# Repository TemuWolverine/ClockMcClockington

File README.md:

# ClockMcClockington
I currently have some “Lenovo Smart Clock Essentials” around the house, but they’ll need to be returned to the original owner soon. Essentially they’re just a segment display with some smarts and a microphone for Google Home.

I’m no fan of voice assistance, so the microphone has been off, meaning they don’t provide much real world value for me other than a clock and that should be easy enough to replicate with an ESP32 and ESPHome.

Since all of the smarts in my house run off Home Assistant (HA), I want this clock to be able to interact with HA. Specifically, I want some buttons that can then trigger other things in the house, such as “shut down all the lights”, or “volume up/down” for the bedroom Sonos speakers. That way I don’t need to have my phone on.

## BoM
| Part | Quantity | Note |
| -----| -------- | ---- |
| [ESP32-S3 Nano](https://s.click.aliexpress.com/e/_c4kUQqIB) | 1 | If you're using the ClockMcClockington PCB, it is designed for this specific ESP32. Otherwise, any S3 with 2MB of PSRAM should be fine |
| [5mm Tactile switches](https://s.click.aliexpress.com/e/_c4DqcA55) | 4 | |
| [GL5516 LDR Photoresistor](https://s.click.aliexpress.com/e/_c41f2RgX) | 1 | |
| [INMP441 Microphone](https://www.aliexpress.com/item/1005006090551057.html) | 1 | |
| [MAX98357a amplifier](https://www.aliexpress.com/item/1005007003802663.html) | 1 | |
| Speaker | 1 | |
|  0.1uf ceramic capacitor | 2| Decoupling, through-hole|
| 10k ohm resistor | 1 | Through-hole|
| ClockMcClockington PCB | 1 | Optional|

## Software
The ESPHome configuration is available as the [yaml file](https://github.com/TemuWolverine/ClockMcClockington/blob/main/clock.yaml), or as a [binary you can flash directly from your browser](https://temuwolverine.github.io/ClockMcClockington/)

### Setup
The temperature information is fetched from Home Assistant. You'll need to have the sensor preconfigured.

* Setup a template sensor
* Navigate (in Home Assistant) to Settings > Devices & Services > Helpers
* Create Helper (bottom right corner) > Template > Sensor
* Two fields are required, the name and the state. Name must be `clock_temp`
* Set the state to `{{ states("sensor.myweathersensor_temperature")}}`
  The other fields are entirely optional, but can make presentation in HomeAssistant clearer 

Alternatively, you can edit the YAML, change `weatherSensor : sensor.clock_temp` to `weatherSensor : sensor.sensor.myweathersensor_temperature`

### Automations
The way ESPHome exposes hardware buttons to Home Assistant is a bit funky (or I'm an idiot and have done it wrong) - they're exposed as generic events rather than 'click'.

ClockMcClockington sends out `esphome.<name>.clock_button_pressed`, where name will start with 'clockmcclockington' plus the MAC of the device. The event data will be one, two, three or four. Currently long press and double click are not implemented. 
```yaml
alias: btnOne
description: ""
triggers:
  - trigger: event
    event_data:
      button: one
    event_type: esphome.clockmcclockingtonred.clock_button_pressed
conditions: []
actions:
  - action: light.toggle
    metadata: {}
    target:
      area_id: study
    data: {}
mode: single
```

## Shell
TODO: 

## Circuit
The Kicad project for the circuit design is available under the [/circuit](https://github.com/TemuWolverine/ClockMcClockington/tree/main/circuit) folder

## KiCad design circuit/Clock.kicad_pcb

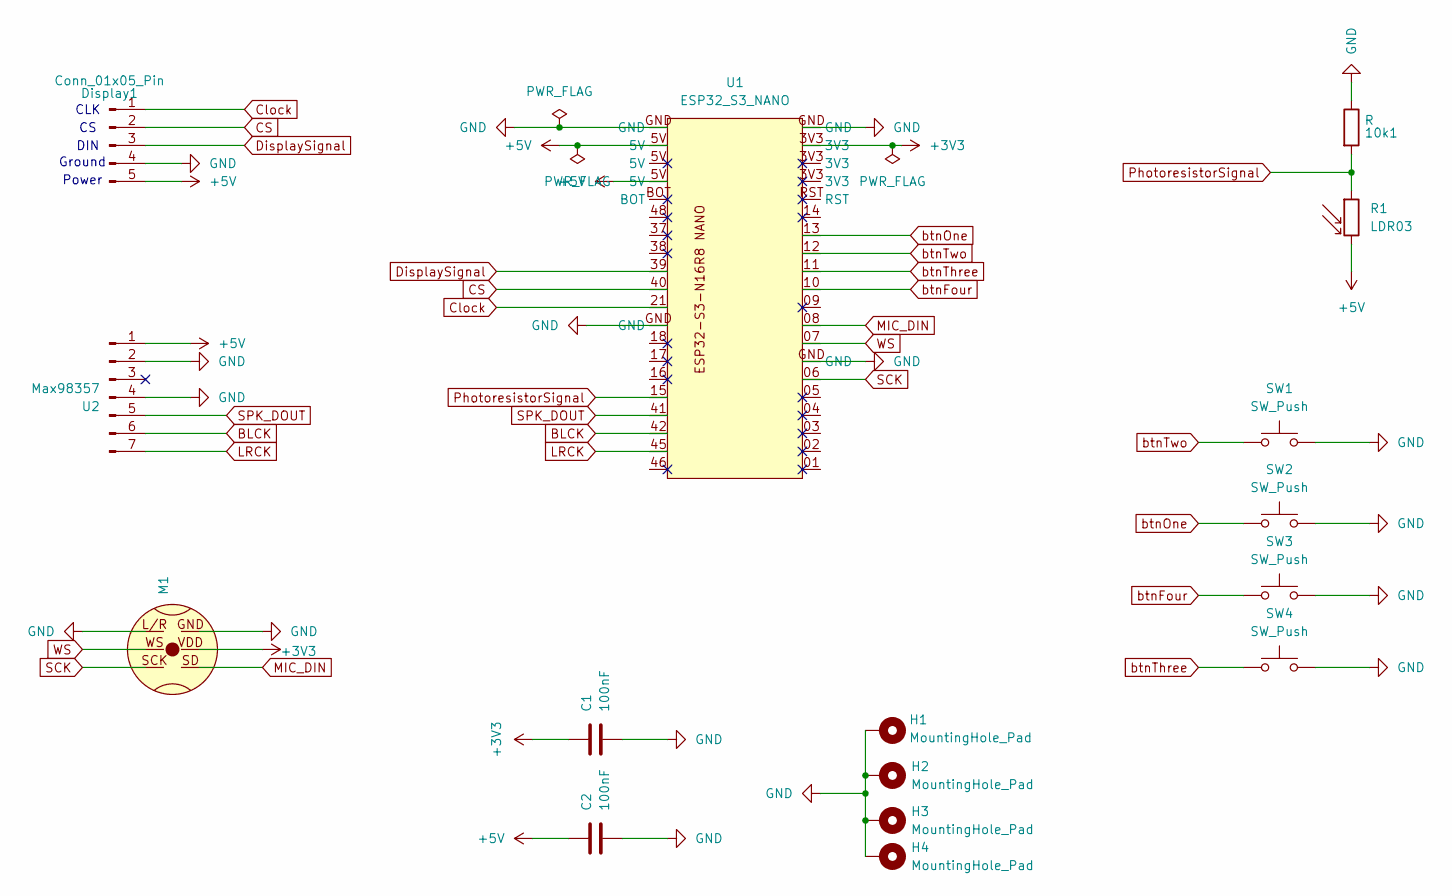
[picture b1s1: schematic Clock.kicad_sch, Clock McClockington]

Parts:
10k1: R; R_Axial_DIN0204_L3.6mm_D1.6mm_P2.54mm_Vertical
C1, C2: 100nF; C_Disc_D8.0mm_W2.5mm_P5.00mm
Display1: Conn_01x05_Pin; PinSocket_1x05_P2.54mm_Vertical
H1, H2, H3, H4: MountingHole_Pad; MountingHole_3.2mm_M3_Pad
M1: INMP441
R1: LDR03; R_LDR_4.9x4.2mm_P2.54mm_Vertical
SW1, SW2, SW3, SW4: SW_Push; SW_PUSH_6mm_H5mm
U1: ESP32_S3_NANO
U2: Max98357; PinHeader_1x07_P2.54mm_Vertical

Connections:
+3V3: C1.1, M1.VDD, U1.3V3
+5V: C2.1, Display1.5, R1.2, U1.5V, U2.1
BLCK: U1.42, U2.6
CS: Display1.2, U1.40
Clock: Display1.1, U1.21
DisplaySignal: Display1.3, U1.39
GND: 10k1.1, C1.2, C2.2, Display1.4, H1.1 (1_1), H2.1 (1_1), H3.1 (1_1), H4.1 (1_1), M1.GND, M1.L/R, SW1.2, SW2.2, SW3.2, SW4.2, U1.GND, U2.2, U2.4
LRCK: U1.45, U2.7
MIC_DIN: M1.SD, U1.08
PhotoresistorSignal: 10k1.2, R1.1, U1.15
SCK: M1.SCK, U1.06
SPK_DOUT: U1.41, U2.5
WS: M1.WS, U1.07
btnFour: SW3.1, U1.10
btnOne: SW2.1, U1.13
btnThree: SW4.1, U1.11
btnTwo: SW1.1, U1.12

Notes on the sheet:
CLK
Power
DIN
Ground

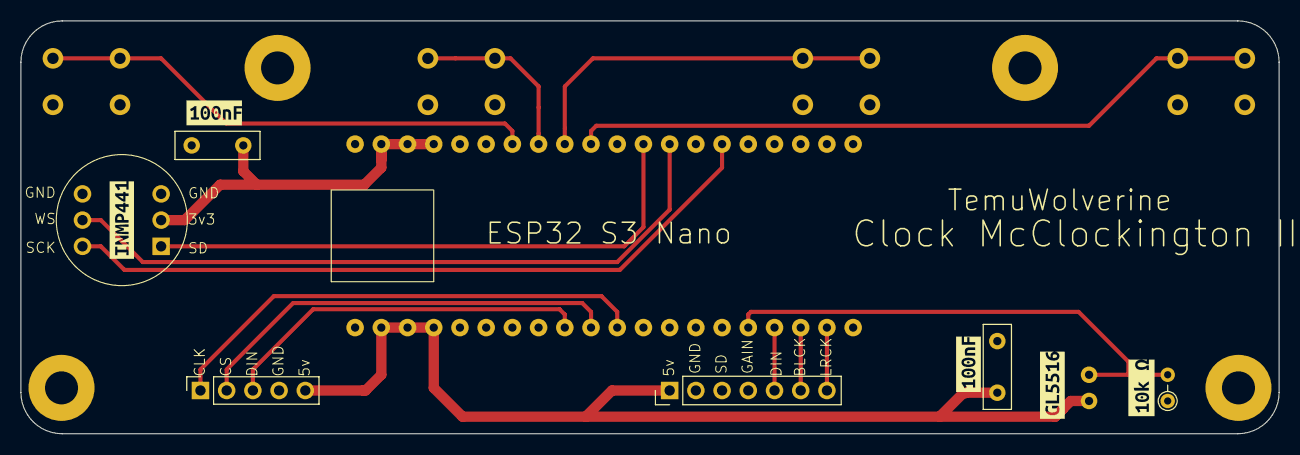
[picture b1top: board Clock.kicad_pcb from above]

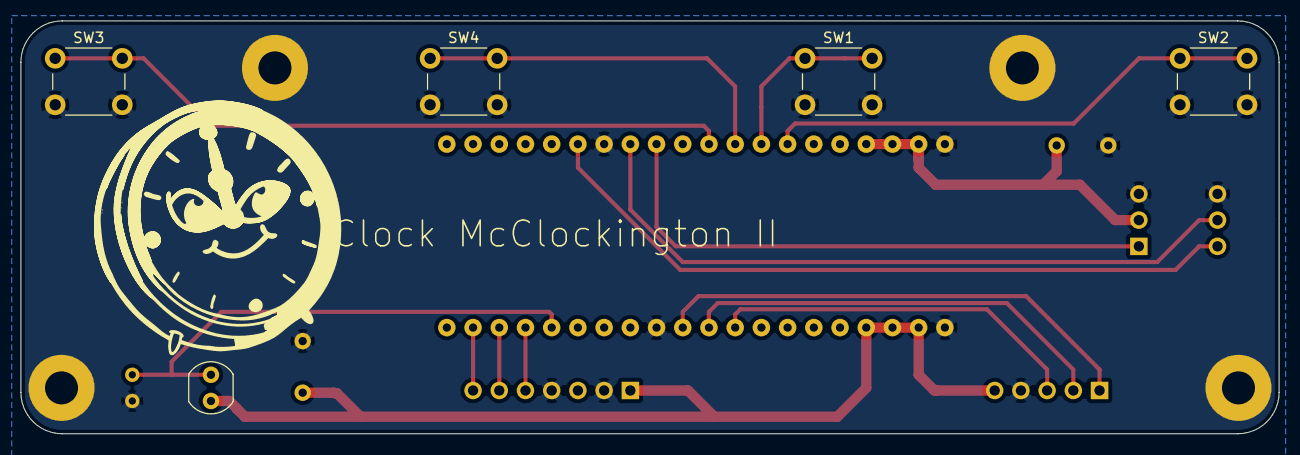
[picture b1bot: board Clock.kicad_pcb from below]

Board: 2 copper layers, 121.9 x 40.0 mm, 21 parts (5 on the bottom side), 17 nets.

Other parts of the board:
kibuzzard-69B74AE8: G***; kibuzzard-69B74AE8
kibuzzard-69B74AF7: G***; kibuzzard-69B74AF7
kibuzzard-69B74B07: G***; kibuzzard-69B74B07
kibuzzard-69B74B24, kibuzzard-69B74B24#2: G***; kibuzzard-69B74B24

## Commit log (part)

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2026-01-16 init
2026-01-16 updated to be gooderer
2026-01-24 rev 1.0 of pcb
2026-02-03 Update Clock PCB nets & footprints
2026-02-03 updated pcb
2026-03-12 ESPHome config now works - needed two I2S channels for input/output. Updated circuit design to reflect this, and better designed PCB/layout with updated ESPS3-zero footprint/symbol
2026-03-13 more tweaks
2026-03-14 switched to mom-switches rather than ttp223 capacitive sensors
2026-03-18 fully functional based on breadboard prototype
2026-03-22 updated to use reusable templates
2026-04-05 design sent to mfg
2026-06-19 added a shared clock config file for snr
2026-06-19 forgot the sensor
2026-06-19 Updated both versions to use shared yaml, adding front matter to all. Probably requires 2026.6 now?
